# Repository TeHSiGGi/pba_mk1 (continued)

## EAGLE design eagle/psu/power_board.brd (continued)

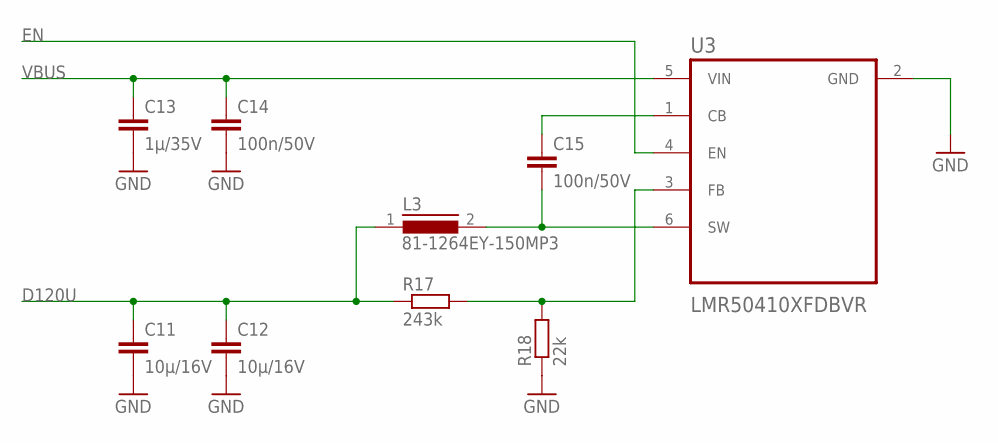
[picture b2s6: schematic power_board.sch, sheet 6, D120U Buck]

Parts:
C11, C12: 10µ/16V; C1206
C13: 1µ/35V; C1206
C14, C15: 100n/50V; C1206
L3: 81-1264EY-150MP3; DR73
R17: 243k; M0805
R18: 22k; M0805
U3: LMR50410XFDBVR; SOT95P280X145-6N

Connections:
D120U: C11.1, C12.1, L3.1, R17.1; also elsewhere on the board
EN: U3.4 (EN); also elsewhere on the board
GND: C11.2, C12.2, C13.2, C14.2, R18.1, U3.2 (GND); also elsewhere on the board
unnamed: C15.1, U3.1 (CB)
unnamed: C15.2, L3.2, U3.6 (SW)
unnamed: R17.2, R18.2, U3.3 (FB)
VBUS: C13.1, C14.1, U3.5 (VIN); also elsewhere on the board

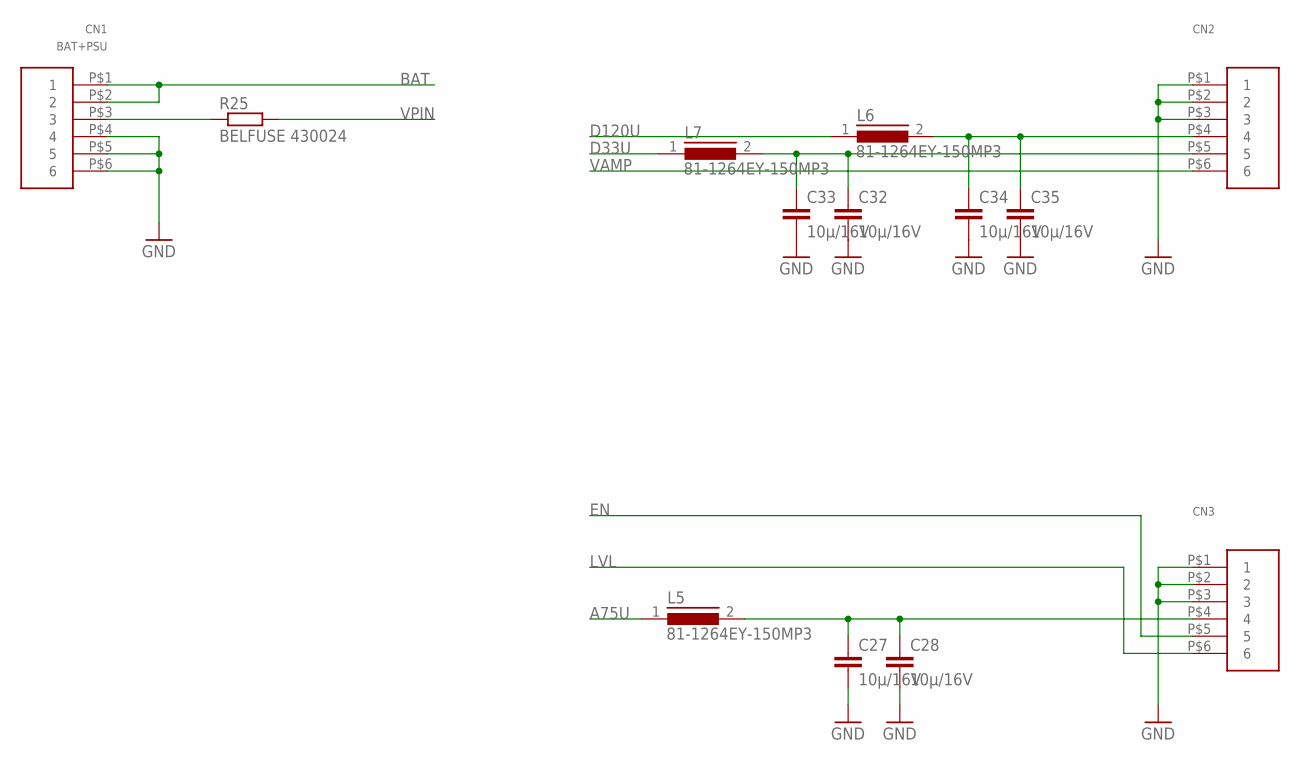
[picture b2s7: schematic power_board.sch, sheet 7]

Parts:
C27, C28, C32, C33, C34, C35: 10µ/16V; C1206
CN1: BAT+PSU; 5569_6P
CN2, CN3: 39-30-1060_BLANK; 5569_6P
L5, L6, L7: 81-1264EY-150MP3; DR73
R25: BELFUSE 430024; R1206W

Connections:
A75U: L5.1; also elsewhere on the board
BAT: CN1.P$1 (1), CN1.P$2 (2); also elsewhere on the board
D33U: L7.1; also elsewhere on the board
D120U: L6.1; also elsewhere on the board
EN: CN3.P$5 (5); also elsewhere on the board
GND: C27.2, C28.2, C32.2, C33.2, C34.2, C35.2, CN1.P$4 (4), CN1.P$5 (5), CN1.P$6 (6), CN2.P$1 (1), CN2.P$2 (2), CN2.P$3 (3), CN3.P$1 (1), CN3.P$2 (2), CN3.P$3 (3); also elsewhere on the board
LVL: CN3.P$6 (6); also elsewhere on the board
unnamed: CN1.P$3 (3), R25.1
unnamed: C27.1, C28.1, CN3.P$4 (4), L5.2
unnamed: C34.1, C35.1, CN2.P$4 (4), L6.2
unnamed: C32.1, C33.1, CN2.P$5 (5), L7.2
VAMP: CN2.P$6 (6); also elsewhere on the board
VPIN: R25.2; also elsewhere on the board

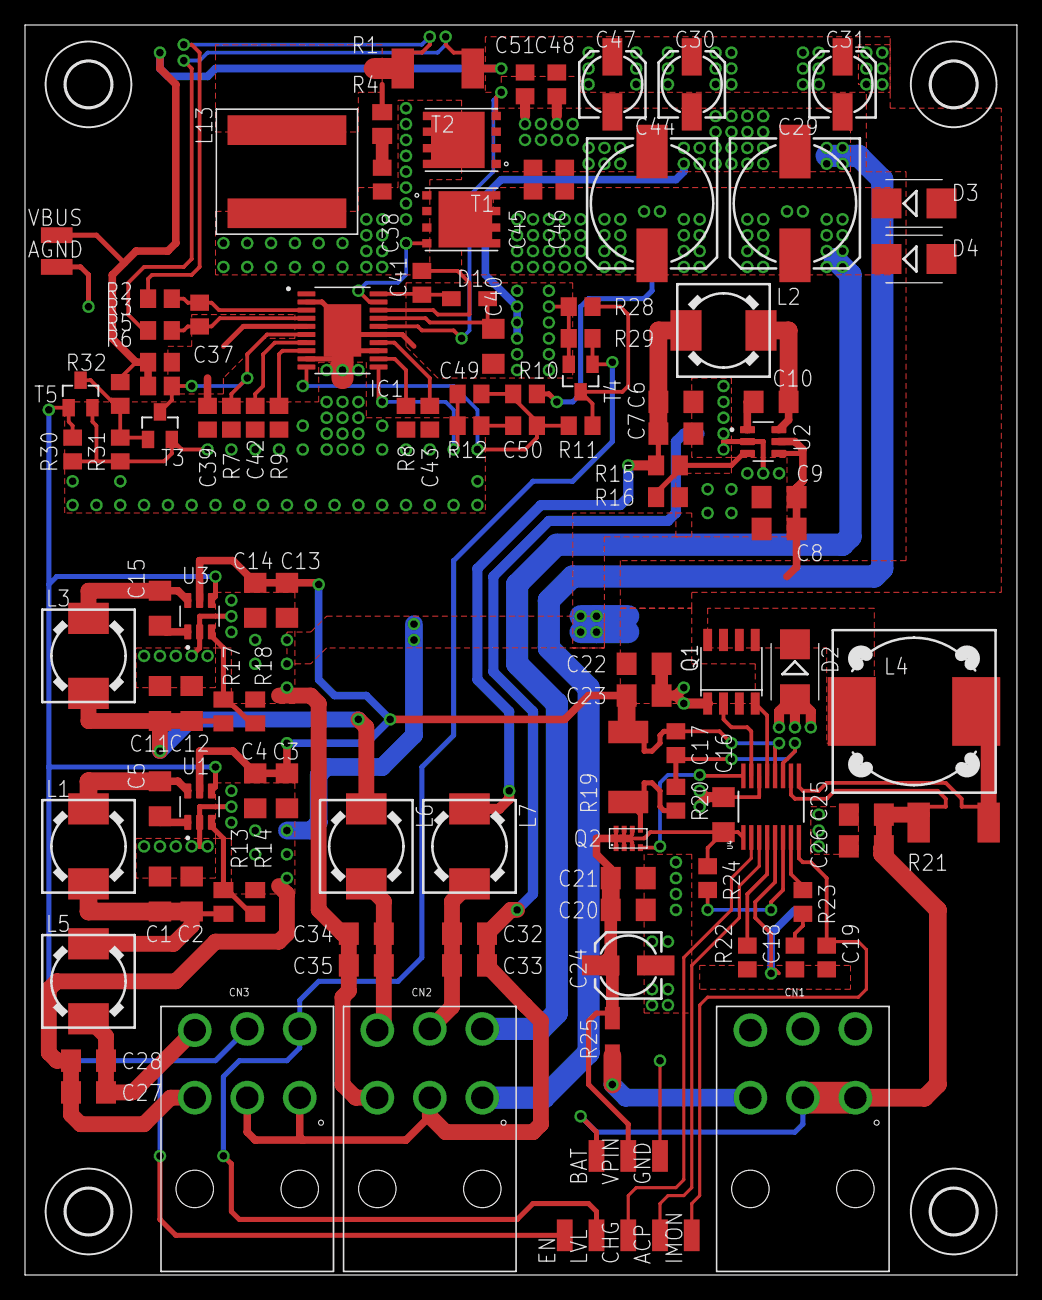
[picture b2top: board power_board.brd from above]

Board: 2 copper layers, 79.4 x 100.0 mm, 121 parts (0 on the bottom side), 57 nets.

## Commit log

2021-05-22 added initial description
2021-05-22 added rawings file
2021-05-22 added eagle and gerber files
2021-05-22 added pdfs
